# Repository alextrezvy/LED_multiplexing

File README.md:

Schematics and PCB of a device which allows to connect 2 7-seg LED displays using 1 shift register 74HC595.
KiCAD project files.

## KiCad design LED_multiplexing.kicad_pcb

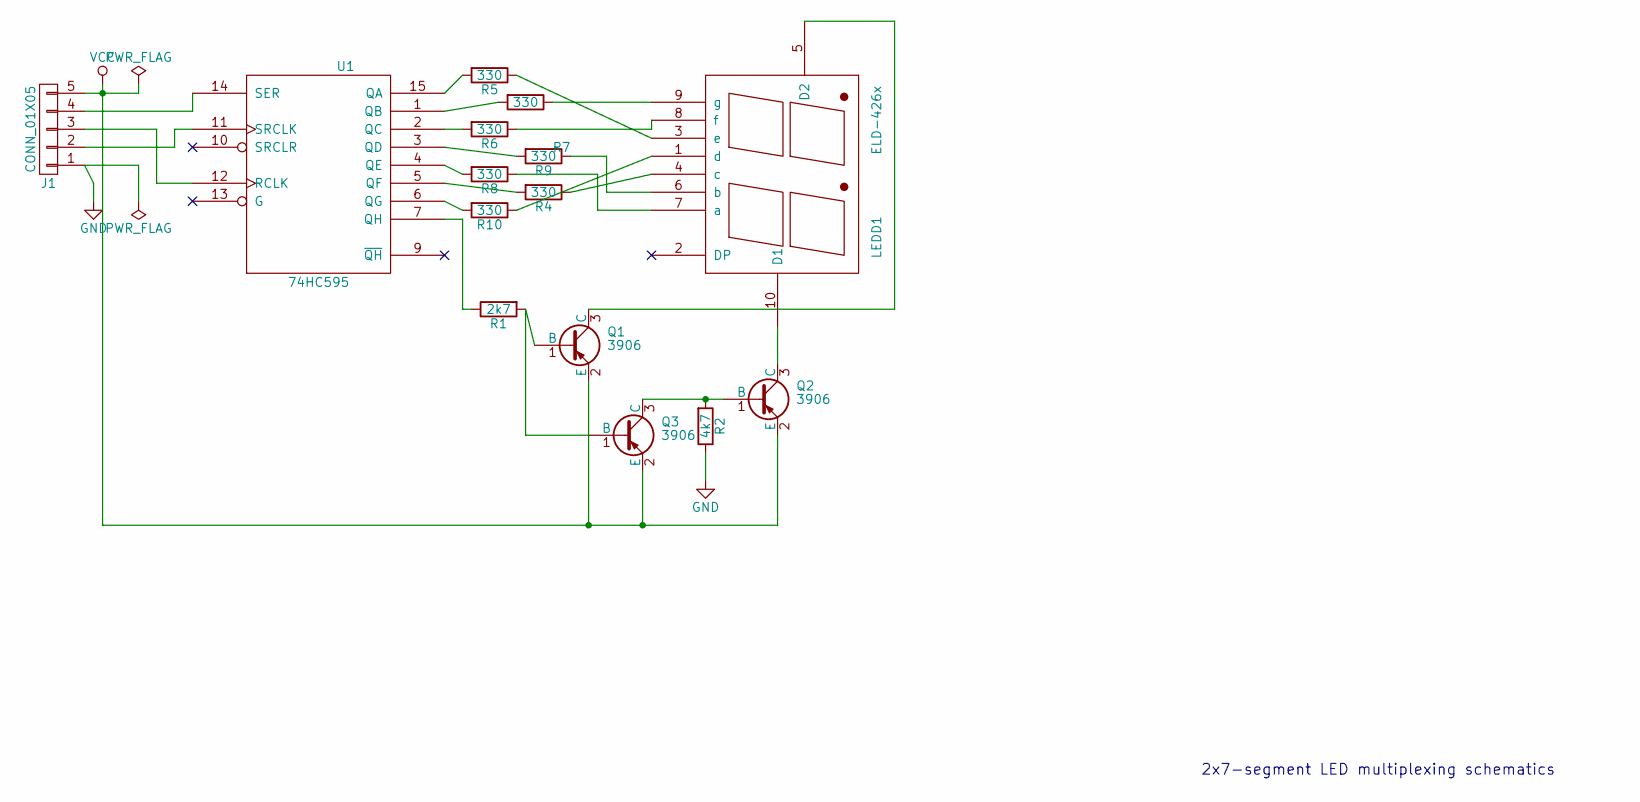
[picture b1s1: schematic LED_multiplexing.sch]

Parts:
J1: CONN_01X05; JST_EH_B05B-EH-A_05x2.50mm_Straight
LEDD1: ELD-426x; ELD_426XXXX
Q1, Q2, Q3: 3906; SOT-23
R1: 2k7; R_0603_HandSoldering
R2: 4k7; R_0603_HandSoldering
R4, R5, R6, R7, R8, R9, R10: 330; R_0603_HandSoldering
U1: 74HC595; SO-16-N

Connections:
GND: J1.1, R2.1, U1.8 (GND)
unnamed: J1.2, U1.11 (SRCLK)
unnamed: J1.3, U1.12 (RCLK)
unnamed: J1.4, U1.14 (SER)
unnamed: LEDD1.1 (d), R10.1
unnamed: LEDD1.3 (e), R5.1
unnamed: LEDD1.4 (c), R4.1
unnamed: LEDD1.5 (D2), Q1.3 (C)
unnamed: LEDD1.6 (b), R9.1
unnamed: LEDD1.7 (a), R8.1
unnamed: LEDD1.8 (f), R6.1
unnamed: LEDD1.9 (g), R7.1
unnamed: LEDD1.10 (D1), Q2.3 (C)
unnamed: Q1.1 (B), Q3.1 (B), R1.2
unnamed: Q2.1 (B), Q3.3 (C), R2.2
unnamed: R1.1, U1.7 (QH)
unnamed: R4.2, U1.5 (QF)
unnamed: R5.2, U1.15 (QA)
unnamed: R6.2, U1.2 (QC)
unnamed: R7.2, U1.1 (QB)
unnamed: R8.2, U1.4 (QE)
unnamed: R9.2, U1.3 (QD)
unnamed: R10.2, U1.6 (QG)
VCC: J1.5, Q1.2 (E), Q2.2 (E), Q3.2 (E), U1.16 (VCC)

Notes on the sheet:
2x7-segment LED multiplexing schematics

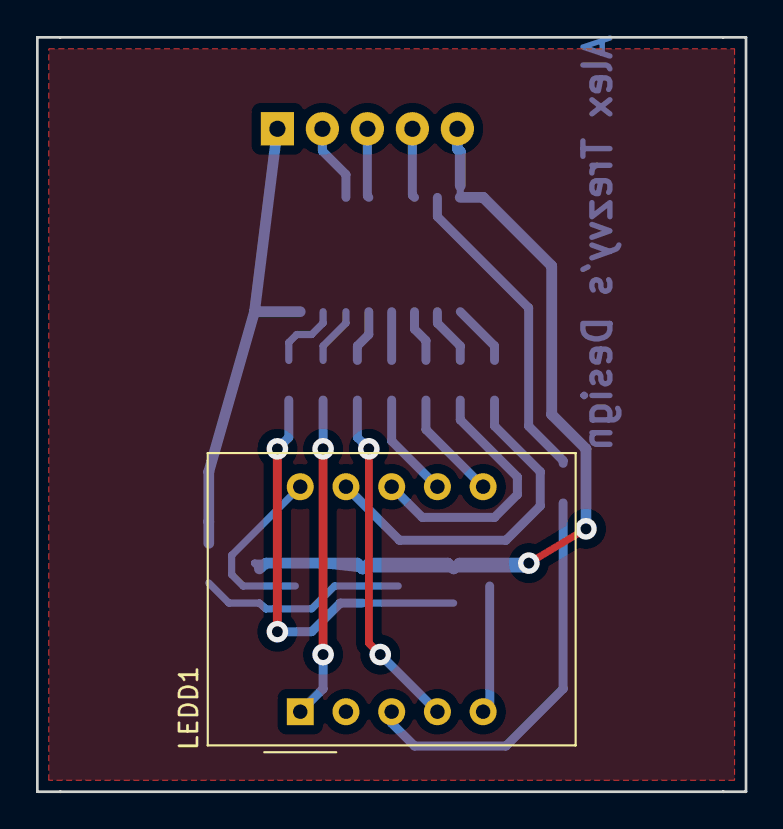
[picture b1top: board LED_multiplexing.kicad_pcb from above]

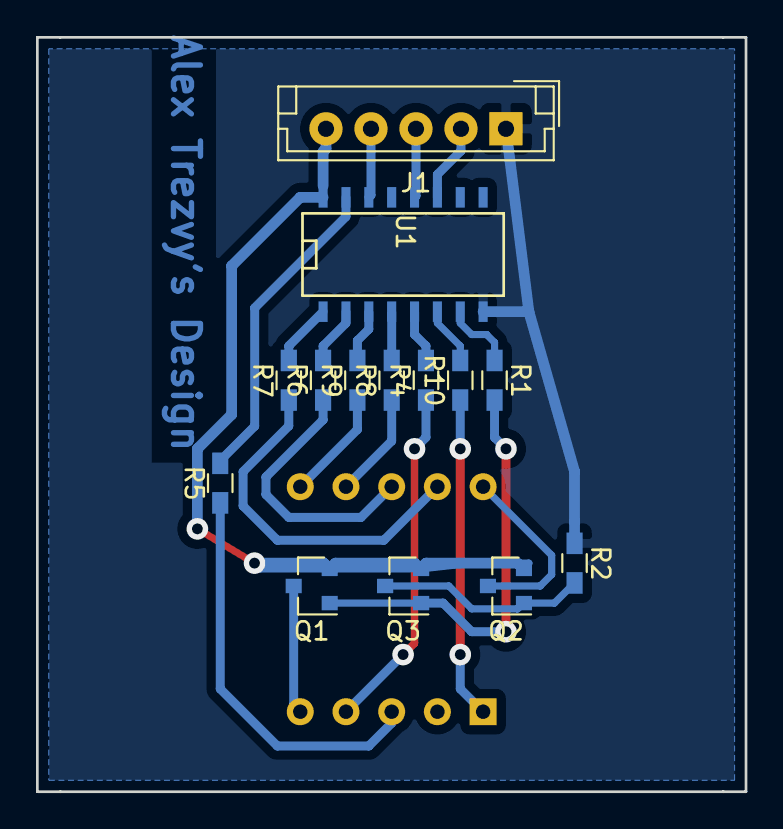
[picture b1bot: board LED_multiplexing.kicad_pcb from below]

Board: 2 copper layers, 39.4 x 41.9 mm, 15 parts (14 on the bottom side), 24 nets.

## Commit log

2018-01-03 Initial placement
2020-03-23 made capacitors larger
